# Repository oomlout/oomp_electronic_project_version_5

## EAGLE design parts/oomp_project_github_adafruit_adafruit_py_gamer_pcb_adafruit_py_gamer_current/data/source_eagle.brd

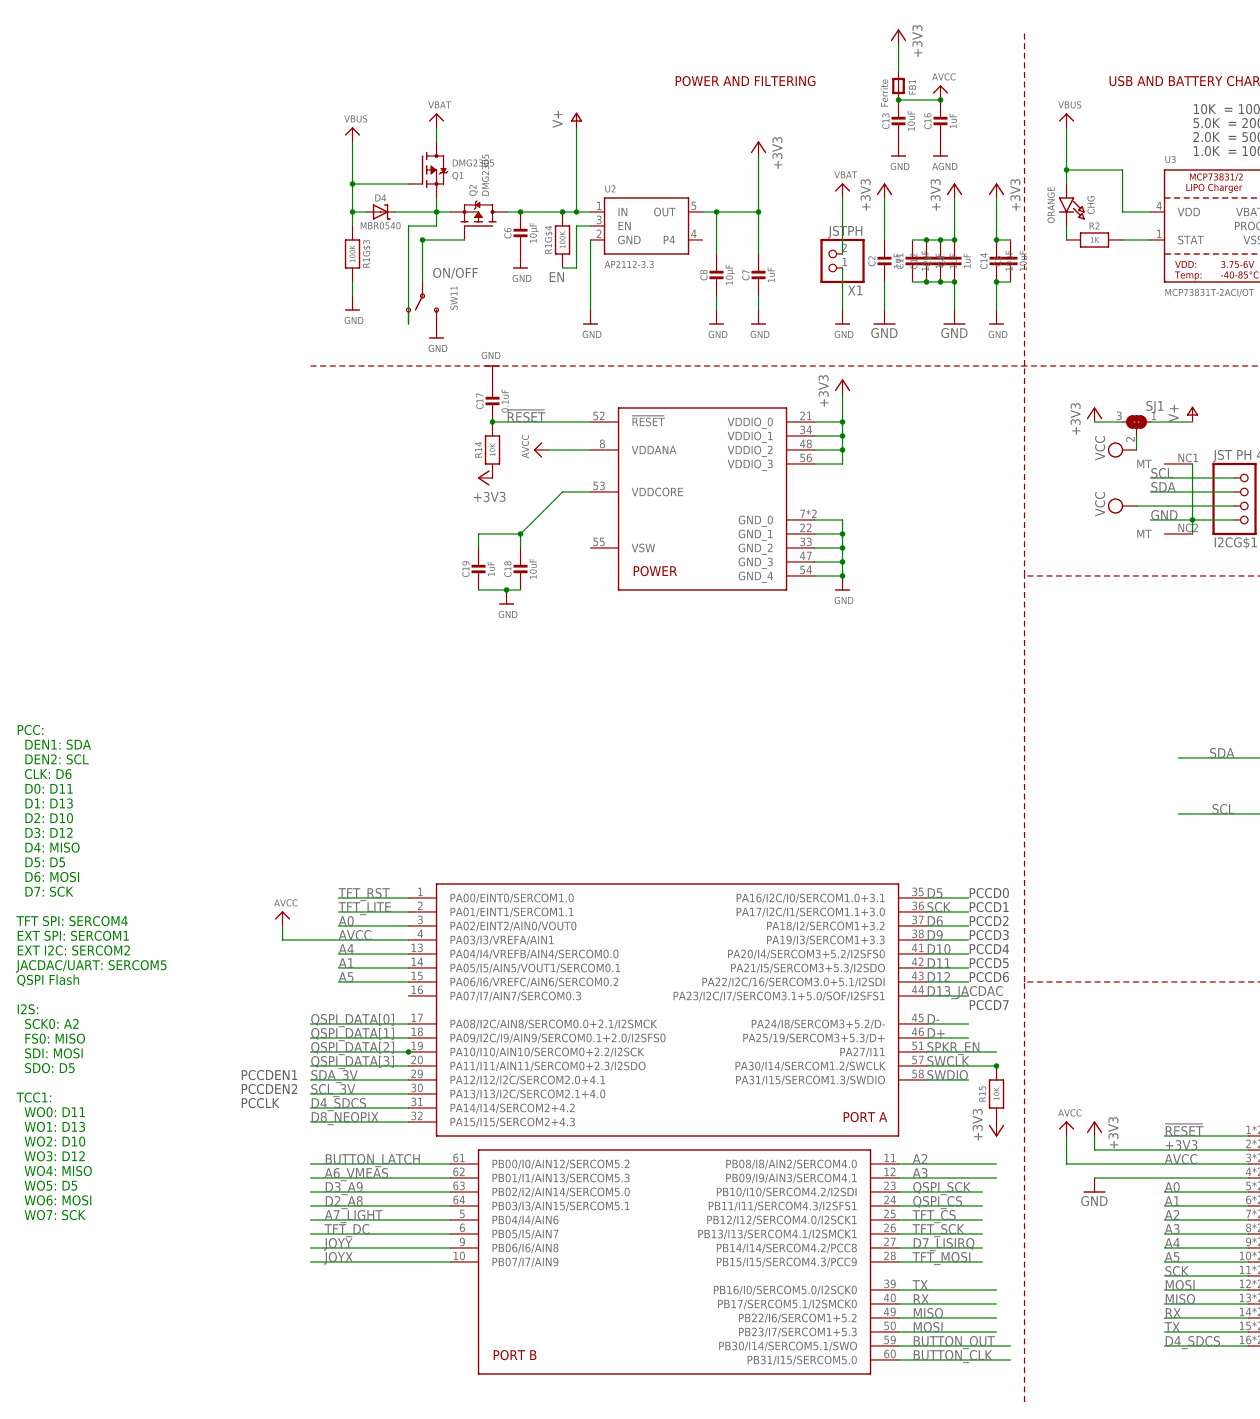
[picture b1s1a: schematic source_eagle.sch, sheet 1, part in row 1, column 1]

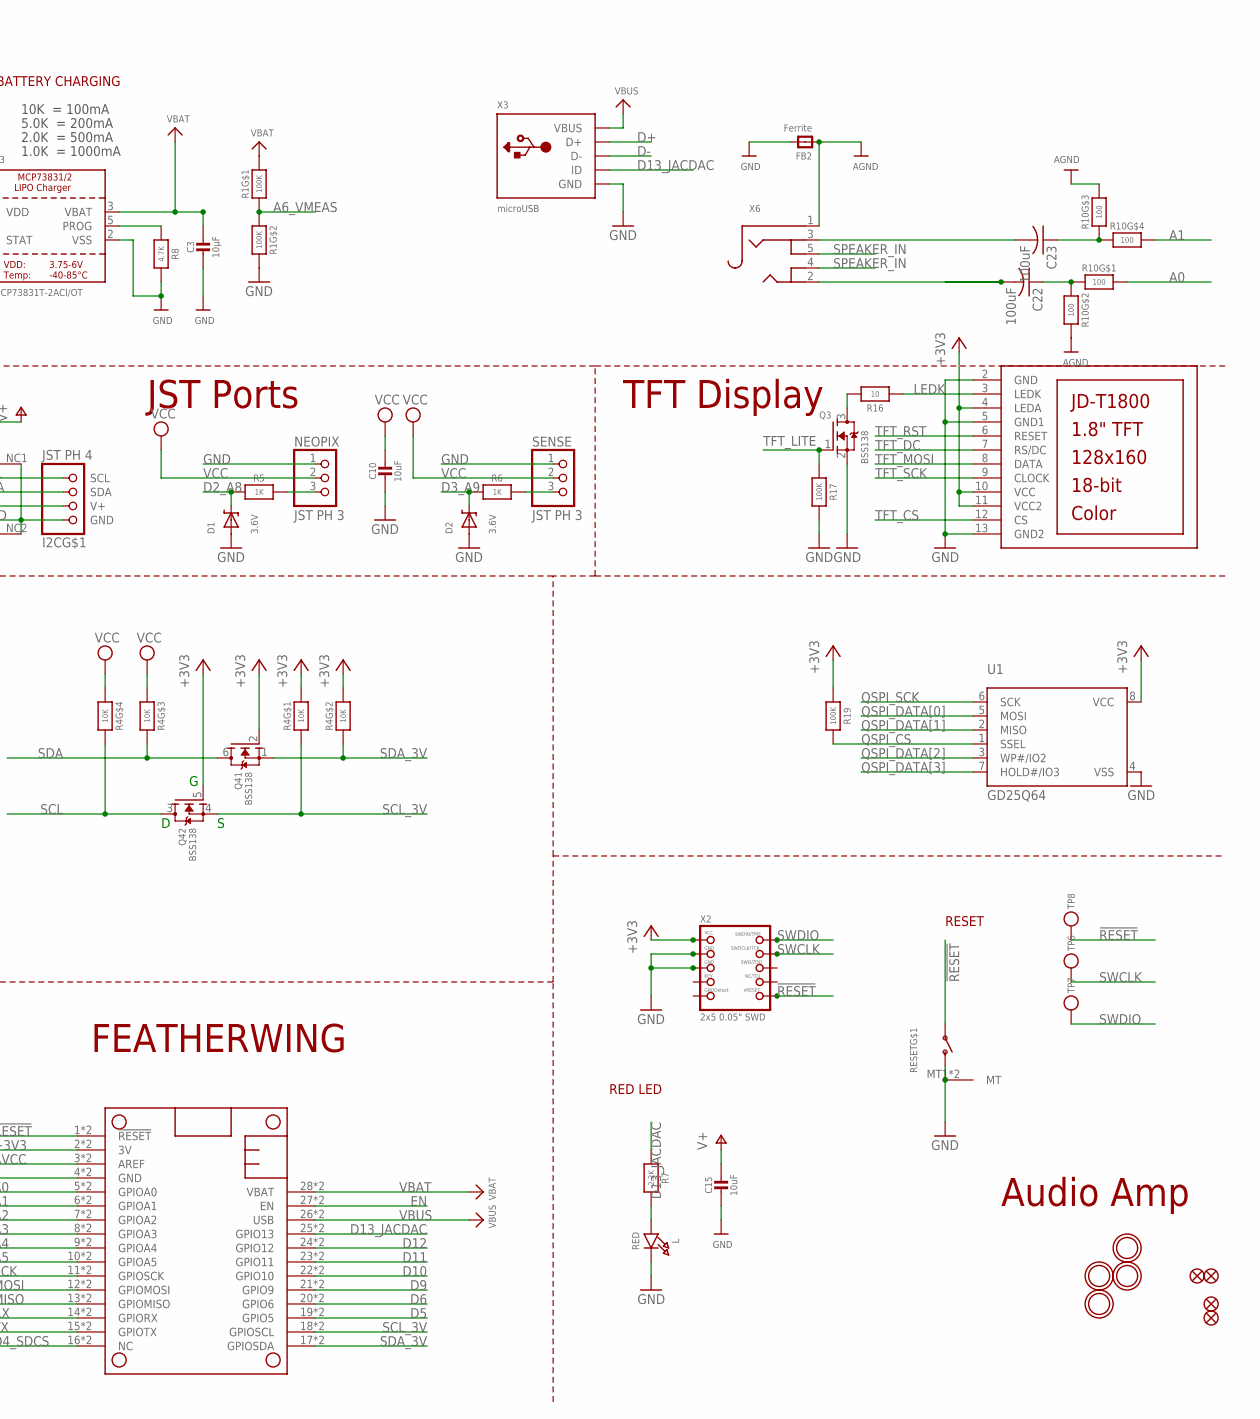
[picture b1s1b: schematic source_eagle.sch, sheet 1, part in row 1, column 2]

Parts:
C1, C2, C4, C7, C12, C16, C19: 1uF; 0603-NO
C3, C6, C8: 10µF; 0805-NO
C5, C10, C11, C13, C14, C15, C18: 10uF; 0805-NO
C17: 0.1uF; 0603-NO
C22, C23: 100uF; C1210
CHG: ORANGE; CHIPLED_0805_NOOUTLINE
D1, D2: 3.6V; SOD-323
D4: MBR0540; SOD-123
FB1: Ferrite; 0805-NO
FB2: Ferrite; _0805MP
I2C: JST PH 4; JSTPH4
L: RED; CHIPLED_0805_NOOUTLINE
LCD1: DISP_LCD_JDT1800; JD-T1800
MS1: FEATHERWING_SMTDUALNOHOLES; FEATHERWING_SMT_NOHOLES
NEOPIX: JST PH 3; JSTPH3
Q1, Q2: DMG2305; SOT23-R
Q3: BSS138; SOT23-WIDE
Q4: BSS138; SOT363
R1: 100K; RESPACK_4X0603
R2, R5, R6: 1K; 0603-NO
R4: 10K; RESPACK_4X0603
R7: 2.2K; 0603-NO
R8: 4.7K; 0603-NO
R10: 100; RESPACK_4X0603
R14, R15: 10K; 0603-NO
R16: 10; 0603-NO
R17, R19: 100K; 0603-NO
RESET: SWITCH_SPST_TACT_RA; SPST_TACTILE_RA
SENSE: JST PH 3; JSTPH3
SJ1: SOLDERJUMPER_2WAY; SOLDERJUMPER_2WAY_OPEN_NOPASTE
SW11: SWITCH_SPDT; SPDT_SMT_SSSS811101
TP6, TP7, TP8: TESTPOINTROUND2MMNO; TESTPOINT_ROUND_2MM_NO
U1: GD25Q64; SOIC8_208MIL
U2: AP2112-3.3; SOT23-5
U3: MCP73831T-2ACI/OT; SOT23-5
U$5, U$6, U$17, U$18: MOUNTINGHOLE3.0THIN; MOUNTINGHOLE_3.0_PLATEDTHIN
U$24: ATSAMD51J19; PQFN64-1
U$34, U$35, U$43, U$46: FIDUCIAL_1MM
X1: JSTPH; JSTPH2
X2: 2x5 0.05" SWD; 2X05_1.27MM_BOX_POSTS
X3: microUSB; 4UCONN_20329_V2
X6: AUDIO_3.5MMJACK; 4UCONN_19269

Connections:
!RESET: C17.2, MS1.1 (!RESET), MS1.1B (!RESET), R14.2, RESET.1, TP8.P$1, U$24.52 (!RESET), X2.10 (NRESET)
+3V3: C1.1, C2.1, C4.1, C5.1, C7.1, C8.1, C11.1, C12.1, C14.1, FB1.1, LCD1.4 (LEDA), LCD1.10 (VCC), LCD1.11 (VCC2), MS1.2 (3V), MS1.2B (3V), Q4.2 (G), Q4.5 (G), R4.1, R4.2 (1), R14.1, R15.1, R19.1, SJ1.3, U1.8 (VCC), U2.5 (OUT), U$24.21 (VDDIO_0), U$24.34 (VDDIO_1), U$24.48 (VDDIO_2), U$24.56 (VDDIO_3), X2.1 (VCC); also elsewhere on the board
A0: MS1.5 (GPIOA0), MS1.5B (GPIOA0), R10.8 (2), U$24.3 (PA02/EINT2/AIN0/VOUT0)
A1: MS1.6 (GPIOA1), MS1.6B (GPIOA1), R10.5 (2), U$24.14 (PA05/I5/AIN5/VOUT1/SERCOM0.1)
A2: MS1.7 (GPIOA2), MS1.7B (GPIOA2), U$24.11 (PB08/I8/AIN2/SERCOM4.0)
A3: MS1.8 (GPIOA3), MS1.8B (GPIOA3), U$24.12 (PB09/I9/AIN3/SERCOM4.1)
A4: MS1.9 (GPIOA4), MS1.9B (GPIOA4), U$24.13 (PA04/I4/VREFB/AIN4/SERCOM0.0)
A5: MS1.10 (GPIOA5), MS1.10B (GPIOA5), U$24.15 (PA06/I6/VREFC/AIN6/SERCOM0.2)
A6_VMEAS: R1.1, R1.2 (1), U$24.62 (PB01/I1/AIN13/SERCOM5.3)
A7_LIGHT: U$24.5 (PB04/I4/AIN6); also elsewhere on the board
AGND: C16.2, FB2.1, R10.6 (2), R10.7 (2), X6.1; also elsewhere on the board
AVCC: C13.1, C16.1, FB1.2, MS1.3 (AREF), MS1.3B (AREF), U$24.4 (PA03/I3/VREFA/AIN1), U$24.8 (VDDANA)
BUTTON_CLK: U$24.60 (PB31/I15/SERCOM5.0); also elsewhere on the board
BUTTON_LATCH: U$24.61 (PB00/I0/AIN12/SERCOM5.2); also elsewhere on the board
BUTTON_OUT: U$24.59 (PB30/I14/SERCOM5.1/SWO); also elsewhere on the board
CHG_LED: R2.2, U3.1 (STAT)
CHG_RATE: R8.1, U3.5 (PROG)
D2_: NEOPIX.3, R5.1
D2_A8: D1.C, R5.2, U$24.64 (PB03/I3/AIN15/SERCOM5.1)
D3_: R6.1, SENSE.3
D3_A9: D2.C, R6.2, U$24.63 (PB02/I2/AIN14/SERCOM5.0)
D4_SDCS: MS1.16 (NC), MS1.16B (NC), U$24.31 (PA14/I14/SERCOM2+4.2); also elsewhere on the board
D5: MS1.19 (GPIO5), MS1.19B (GPIO5), U$24.35 (PA16/I2C/I0/SERCOM1.0+3.1)
D6: MS1.20 (GPIO6), MS1.20B (GPIO6), U$24.37 (PA18/I2/SERCOM1+3.2)
D7_LISIRQ: U$24.27 (PB14/I14/SERCOM4.2/PCC8); also elsewhere on the board
D8_NEOPIX: U$24.32 (PA15/I15/SERCOM2+4.3); also elsewhere on the board
D9: MS1.21 (GPIO9), MS1.21B (GPIO9), U$24.38 (PA19/I3/SERCOM1+3.3)
D10: MS1.22 (GPIO10), MS1.22B (GPIO10), U$24.41 (PA20/I4/SERCOM3+5.2/I2SFS0)
D11: MS1.23 (GPIO11), MS1.23B (GPIO11), U$24.42 (PA21/I5/SERCOM3+5.3/I2SDO)
D12: MS1.24 (GPIO12), MS1.24B (GPIO12), U$24.43 (PA22/I2C/16/SERCOM3.0+5.1/I2SDI)
D13_JACDAC: MS1.25 (GPIO13), MS1.25B (GPIO13), R7.1, U$24.44 (PA23/I2C/I7/SERCOM3.1+5.0/SOF/I2SFS1), X3.ID
D+: U$24.46 (PA25/19/SERCOM3+5.3/D+), X3.D+
D-: U$24.45 (PA24/I8/SERCOM3+5.2/D-), X3.D-
EN: MS1.27 (EN), MS1.27B (EN), R1.4 (1), U2.3 (EN)
GND: C1.2, C2.2, C3.2, C4.2, C5.2, C6.2, C7.2, C8.2, C10.2, C11.2, C12.2, C13.2, C14.2, C15.2, C17.1, C18.2, C19.2, D1.A, D2.A, FB2.2, I2C.1 (GND), I2C.NC1 (MT), I2C.NC2 (MT), L.C, LCD1.2 (GND), LCD1.5 (GND1), LCD1.13 (GND2), MS1.4 (GND), MS1.4B (GND), NEOPIX.1, Q3.2 (S), R1.6 (2), R1.7 (2), R8.2, R17.2, RESET.2 (S), RESET.MT1 (MT), RESET.MT2 (MT), SENSE.1, SW11.C (S), U1.4 (VSS), U2.2 (GND), U3.2 (VSS), U$24.7 (GND_0), U$24.22 (GND_1), U$24.33 (GND_2), U$24.47 (GND_3), U$24.54 (GND_4), U$24.EXP (GND_0), X1.1, X2.3 (GND), X2.5 (GND), X3.BASE@1 (GND), X3.BASE@2 (GND), X3.GND, X3.SPRT@1 (GND), X3.SPRT@2 (GND), X3.SPRT@3 (GND), X3.SPRT@4 (GND); also elsewhere on the board
JOYX: U$24.10 (PB07/I7/AIN9); also elsewhere on the board
JOYY: U$24.9 (PB06/I6/AIN8); also elsewhere on the board
LEDK: LCD1.3 (LEDK), R16.1
MISO: MS1.13 (GPIOMISO), MS1.13B (GPIOMISO), U$24.49 (PB22/I6/SERCOM1+5.2); also elsewhere on the board
MOSI: MS1.12 (GPIOMOSI), MS1.12B (GPIOMOSI), U$24.50 (PB23/I7/SERCOM1+5.3); also elsewhere on the board
unnamed: CHG.C, R2.1
unnamed: L.A, R7.2
unnamed: Q3.3 (D), R16.2
unnamed: D4.C, Q1.2 (S), Q2.2 (S), SW11.A (O)
unnamed: C23.2, X6.3
unnamed: C22.2, X6.2
unnamed: C23.1, R10.3 (1), R10.4 (1)
unnamed: C22.1, R10.1, R10.2 (1)
ON/OFF: Q2.1 (G), SW11.B
QSPI_CS: R19.2, U1.1 (SSEL), U$24.24 (PB11/I11/SERCOM4.3/I2SFS1)
QSPI_DATA[0]: U1.5 (MOSI), U$24.17 (PA08/I2C/AIN8/SERCOM0.0+2.1/I2SMCK)
QSPI_DATA[1]: U1.2 (MISO), U$24.18 (PA09/I2C/I9/AIN9/SERCOM0.1+2.0/I2SFS0)
QSPI_DATA[2]: U1.3 (WP#/IO2), U$24.19 (PA10/I10/AIN10/SERCOM0+2.2/I2SCK)
QSPI_DATA[3]: U1.7 (HOLD#/IO3), U$24.20 (PA11/I11/AIN11/SERCOM0+2.3/I2SDO)
QSPI_SCK: U1.6 (SCK), U$24.23 (PB10/I10/SERCOM4.2/I2SDI)
RX: MS1.14 (GPIORX), MS1.14B (GPIORX), U$24.40 (PB17/SERCOM5.1/I2SMCK0)
SCK: MS1.11 (GPIOSCK), MS1.11B (GPIOSCK), U$24.36 (PA17/I2C/I1/SERCOM1.1+3.0); also elsewhere on the board
SCL: I2C.4 (SCL), Q4.3 (D), R4.5 (2)
SCL_3V: MS1.18 (GPIOSCL), MS1.18B (GPIOSCL), Q4.4 (S), R4.8 (2), U$24.30 (PA13/I13/I2C/SERCOM2.1+4.0); also elsewhere on the board
SDA: I2C.3 (SDA), Q4.6 (D), R4.6 (2)
SDA_3V: MS1.17 (GPIOSDA), MS1.17B (GPIOSDA), Q4.1 (S), R4.7 (2), U$24.29 (PA12/I12/I2C/SERCOM2.0+4.1); also elsewhere on the board
SPEAKER_IN: X6.4, X6.5; also elsewhere on the board
SPKR_EN: U$24.51 (PA27/I11); also elsewhere on the board
SWCLK: R15.2, TP6.P$1, U$24.57 (PA30/I14/SERCOM1.2/SWCLK), X2.4 (SWDCLK)
SWDIO: TP7.P$1, U$24.58 (PA31/I15/SERCOM1.3/SWDIO), X2.2 (SWDIO)
TFT_CS: LCD1.12 (CS), U$24.25 (PB12/I12/SERCOM4.0/I2SCK1)
TFT_DC: LCD1.7 (RS/DC), U$24.6 (PB05/I5/AIN7)
TFT_LITE: Q3.1 (G), R17.1, U$24.2 (PA01/EINT1/SERCOM1.1)
TFT_MOSI: LCD1.8 (DATA), U$24.28 (PB15/I15/SERCOM4.3/PCC9)
TFT_RST: LCD1.6 (RESET), U$24.1 (PA00/EINT0/SERCOM1.0)
TFT_SCK: LCD1.9 (CLOCK), U$24.26 (PB13/I13/SERCOM4.1/I2SMCK1)
TX: MS1.15 (GPIOTX), MS1.15B (GPIOTX), U$24.39 (PB16/I0/SERCOM5.0/I2SCK0)
V+: C6.1, C15.1, Q2.3 (D), R1.5 (2), SJ1.1, U2.1 (IN); also elsewhere on the board
VBAT: C3.1, MS1.28 (VBAT), MS1.28B (VBAT), Q1.3 (D), R1.8 (2), U3.3 (VBAT), X1.2
VBUS: CHG.A, D4.A, MS1.26 (USB), MS1.26B (USB), Q1.1 (G), R1.3 (1), U3.4 (VDD), X3.VBUS
VCC: C10.1, I2C.2 (V+), NEOPIX.2, R4.3 (1), R4.4 (1), SENSE.2, SJ1.2
VDDCORE2: C18.1, C19.1, U$24.53 (VDDCORE)

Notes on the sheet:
POWER AND FILTERING
RESET
10K = 100mA
5.0K = 200mA
2.0K = 500mA
1.0K = 1000mA
USB AND BATTERY CHARGING
RED LED
FEATHERWING
TFT Display
Audio Amp
JST Ports
PCCDEN1
PCCDEN2
PCCD0
PCCD1
PCCD2
PCCD3
PCCD4
PCCD5
PCCD6
PCCD7
PCCLK
PCC: DEN1: SDA DEN2: SCL CLK: D6 D0: D11 D1: D13 D2: D10 D3: D12 D4: MISO D5: D5 D6: MOSI D7: SCK TFT SPI: SERCOM4 EXT SPI: SERCOM1 EXT I2C: SERCOM2 JACDAC/UART: SERCOM5 QSPI Flash I2S: SCK0: A2 FS0: MISO SDI: MOSI SDO: D5 TCC1: WO0: D11 WO1: D13 WO2: D10 WO3: D12 WO4: MISO WO5: D5 WO6: MOSI WO7: S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

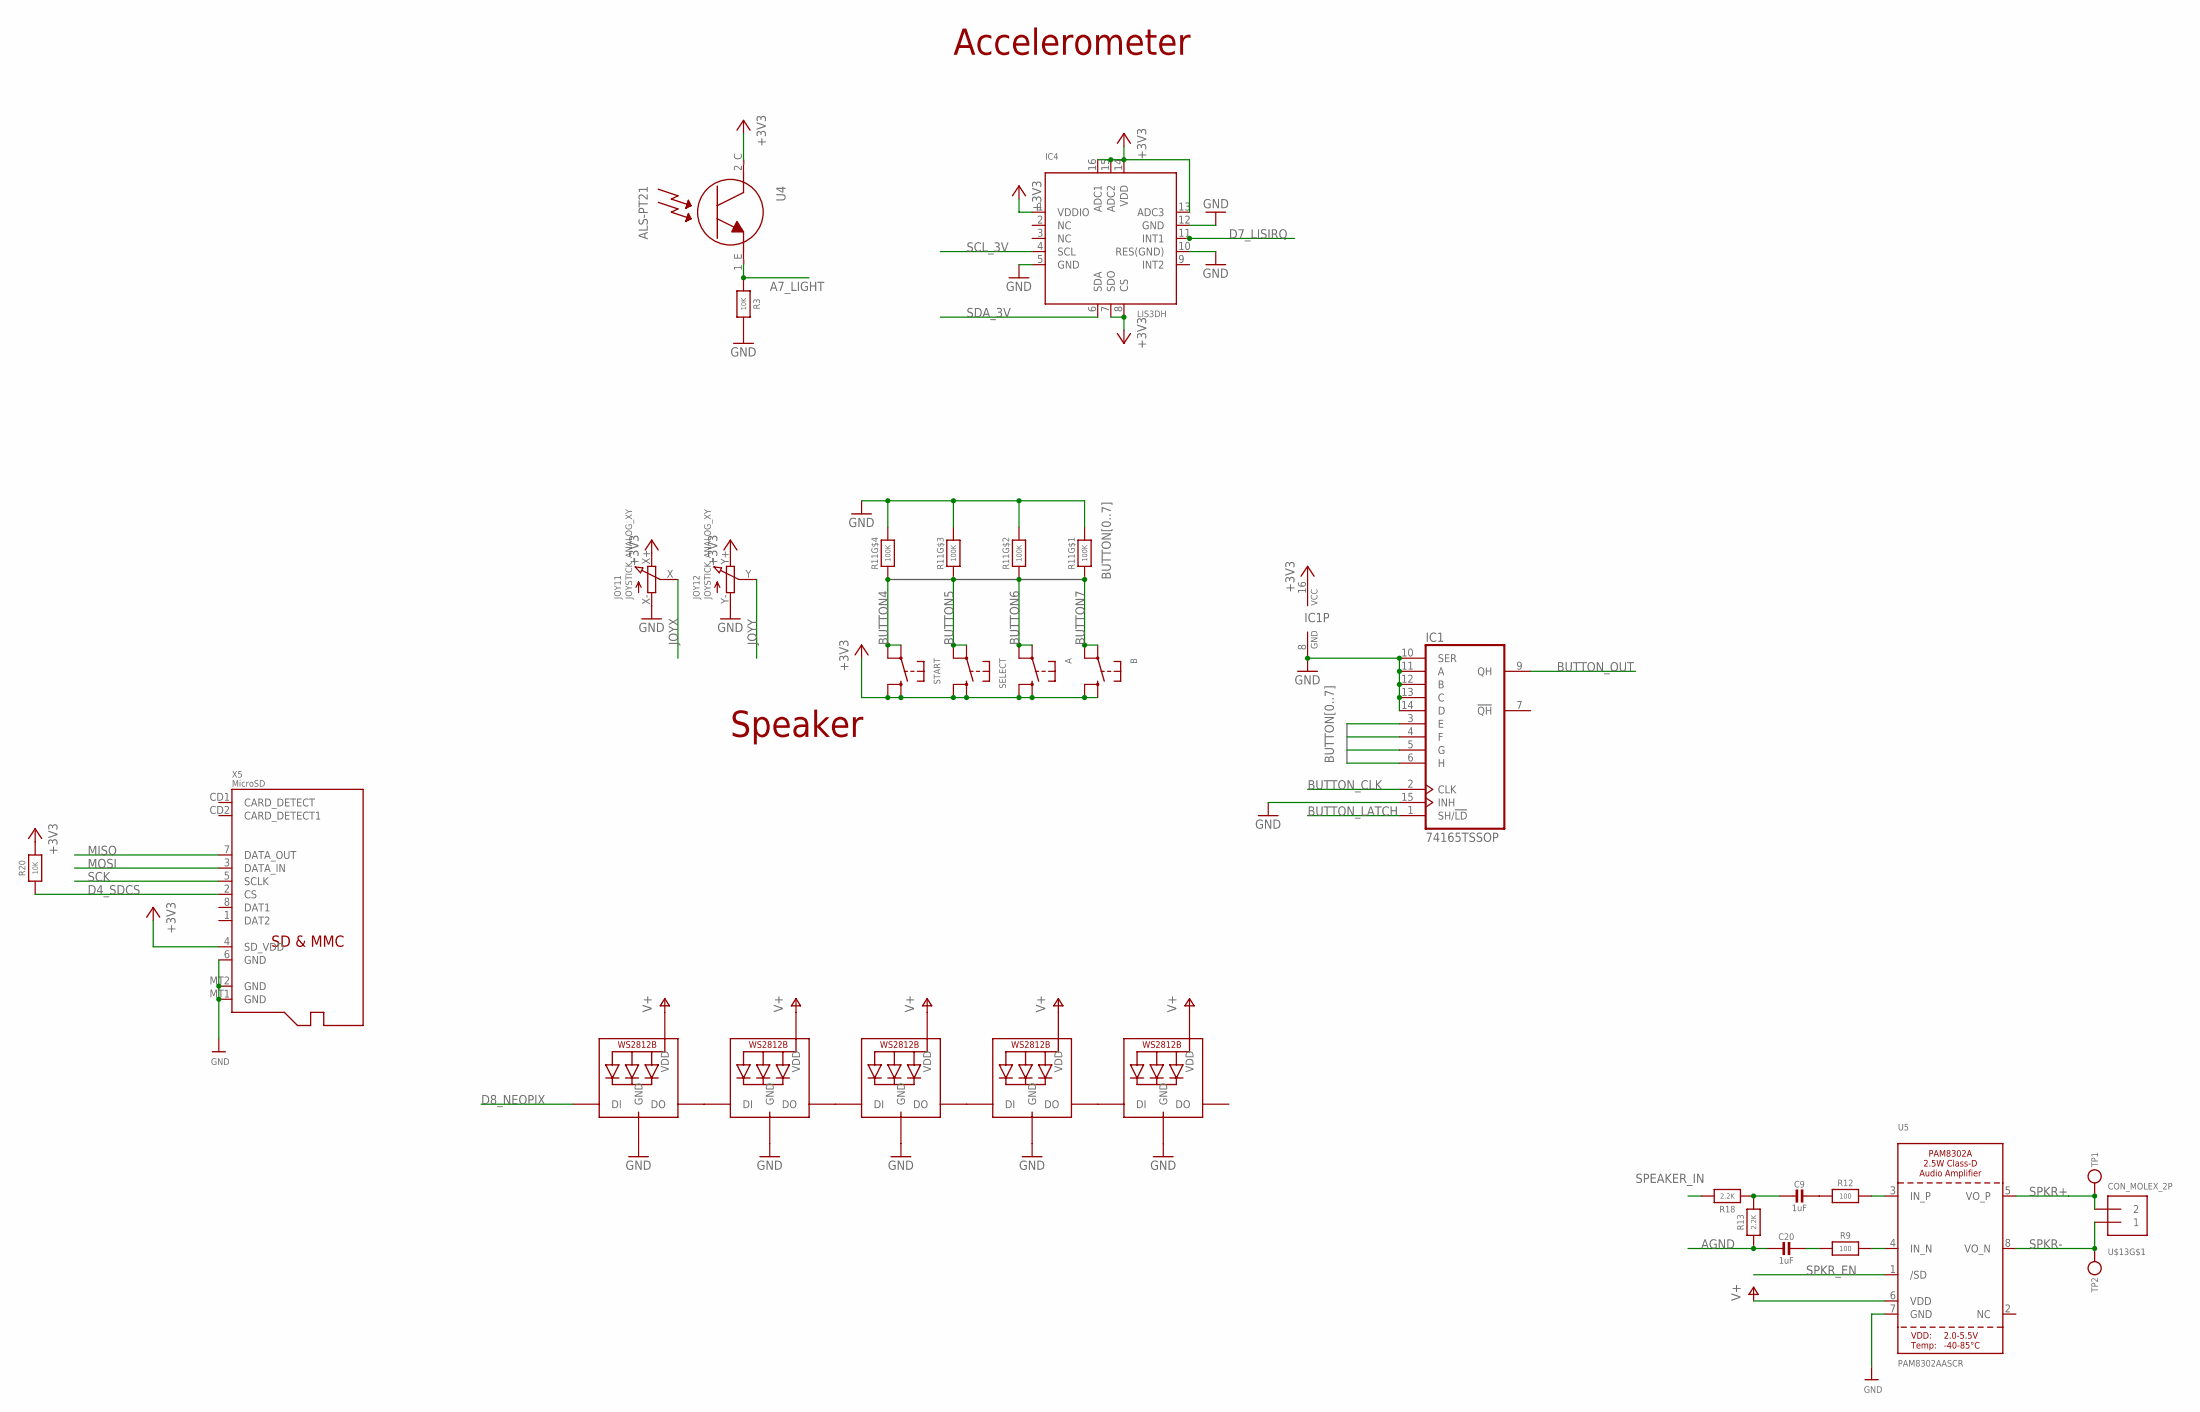
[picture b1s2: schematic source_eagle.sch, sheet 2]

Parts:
A: SWITCH_TACT_SMT_6MM8MMCAP; 6MM_SMT_6MMCAP
B: SWITCH_TACT_SMT_6MM8MMCAP; 6MM_SMT_6MMCAP
C9, C20: 1uF; 0603-NO
IC1: 74165TSSOP; TSSOP16
IC4: LIS3DH; LGA16_3X3MM
JOY1: JOYSTICK_ANALOG_XY; JOYSTICK_ANALOG_MINITHM
LED1, LED2, LED3, LED4, LED5: WS2812B3535; LED3535
R3, R20: 10K; 0603-NO
R9, R12: 100; 0603-NO
R11: 100K; RESPACK_4X0603
R13, R18: 2.2K; 0603-NO
SELECT: SWITCH_TACT_SMT_6MM8MMCAP; 6MM_SMT_6MMCAP
START: SWITCH_TACT_SMT_6MM8MMCAP; 6MM_SMT_6MMCAP
TP1, TP2: TESTPOINTROUND1.5MMNO; TESTPOINT_ROUND_1.5MM_NO
U4: ALS-PT21; ALS-PT26-21C
U5: PAM8302AASCR; MSOP8_0.65MM
U$13: CON_MOLEX_2P; 53398-0271
X5: MicroSD; MICROSD

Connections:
+3V3: A.B (S), A.B' (S1), B.B (S), B.B' (S1), IC1.16 (VCC), IC4.1 (VDDIO), IC4.7 (SDO), IC4.8 (CS), IC4.13 (ADC3), IC4.14 (VDD), IC4.15 (ADC2), IC4.16 (ADC1), JOY1.X+ (E), JOY1.Y+ (E), R20.2, SELECT.B (S), SELECT.B' (S1), START.B (S), START.B' (S1), U4.2_C (C), X5.4 (SD_VDD); also elsewhere on the board
A7_LIGHT: R3.2, U4.1_E (E); also elsewhere on the board
AGND: C20.2, R13.1; also elsewhere on the board
BUTTON4: IC1.3 (E), R11.4 (1), START.A, START.A' (P1)
BUTTON5: IC1.4 (F), R11.3 (1), SELECT.A, SELECT.A' (P1)
BUTTON6: A.A, A.A' (P1), IC1.5 (G), R11.2 (1)
BUTTON7: B.A, B.A' (P1), IC1.6 (H), R11.1
BUTTON_CLK: IC1.2 (CLK); also elsewhere on the board
BUTTON_LATCH: IC1.1 (SH/!LD); also elsewhere on the board
BUTTON_OUT: IC1.9 (QH); also elsewhere on the board
D4_SDCS: R20.1, X5.2 (CS); also elsewhere on the board
D7_LISIRQ: IC4.11 (INT1); also elsewhere on the board
D8_NEOPIX: LED1.1 (DI); also elsewhere on the board
GND: IC1.8 (GND), IC1.10 (SER), IC1.11 (A), IC1.12 (B), IC1.13 (C), IC1.14 (D), IC1.15 (INH), IC4.5 (GND), IC4.10 (RES(GND)), IC4.12 (GND), JOY1.X- (A), JOY1.Y- (A), LED1.4 (GND), LED2.4 (GND), LED3.4 (GND), LED4.4 (GND), LED5.4 (GND), R3.1, R11.5 (2), R11.6 (2), R11.7 (2), R11.8 (2), U5.7 (GND), X5.6 (GND), X5.MT1 (GND), X5.MT2 (GND); also elsewhere on the board
JOYX: JOY1.X (S); also elsewhere on the board
JOYY: JOY1.Y (S); also elsewhere on the board
MISO: X5.7 (DATA_OUT); also elsewhere on the board
MOSI: X5.3 (DATA_IN); also elsewhere on the board
unnamed: LED1.3 (DO), LED2.1 (DI)
unnamed: LED2.3 (DO), LED3.1 (DI)
unnamed: LED3.3 (DO), LED4.1 (DI)
unnamed: LED4.3 (DO), LED5.1 (DI)
unnamed: R9.2, U5.4 (IN_N)
unnamed: R12.2, U5.3 (IN_P)
unnamed: C9.2, R13.2, R18.1
unnamed: C20.1, R9.1
unnamed: C9.1, R12.1
SCK: X5.5 (SCLK); also elsewhere on the board
SCL_3V: IC4.4 (SCL); also elsewhere on the board
SDA_3V: IC4.6 (SDA); also elsewhere on the board
SPEAKER_IN: R18.2; also elsewhere on the board
SPKR+: TP1.P$1, U5.5 (VO_P), U$13.2
SPKR-: TP2.P$1, U5.8 (VO_N), U$13.1
SPKR_EN: U5.1 (/SD); also elsewhere on the board
V+: LED1.2 (VDD), LED2.2 (VDD), LED3.2 (VDD), LED4.2 (VDD), LED5.2 (VDD), U5.6 (VDD); also elsewhere on the board

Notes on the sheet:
Speaker
Accelerometer

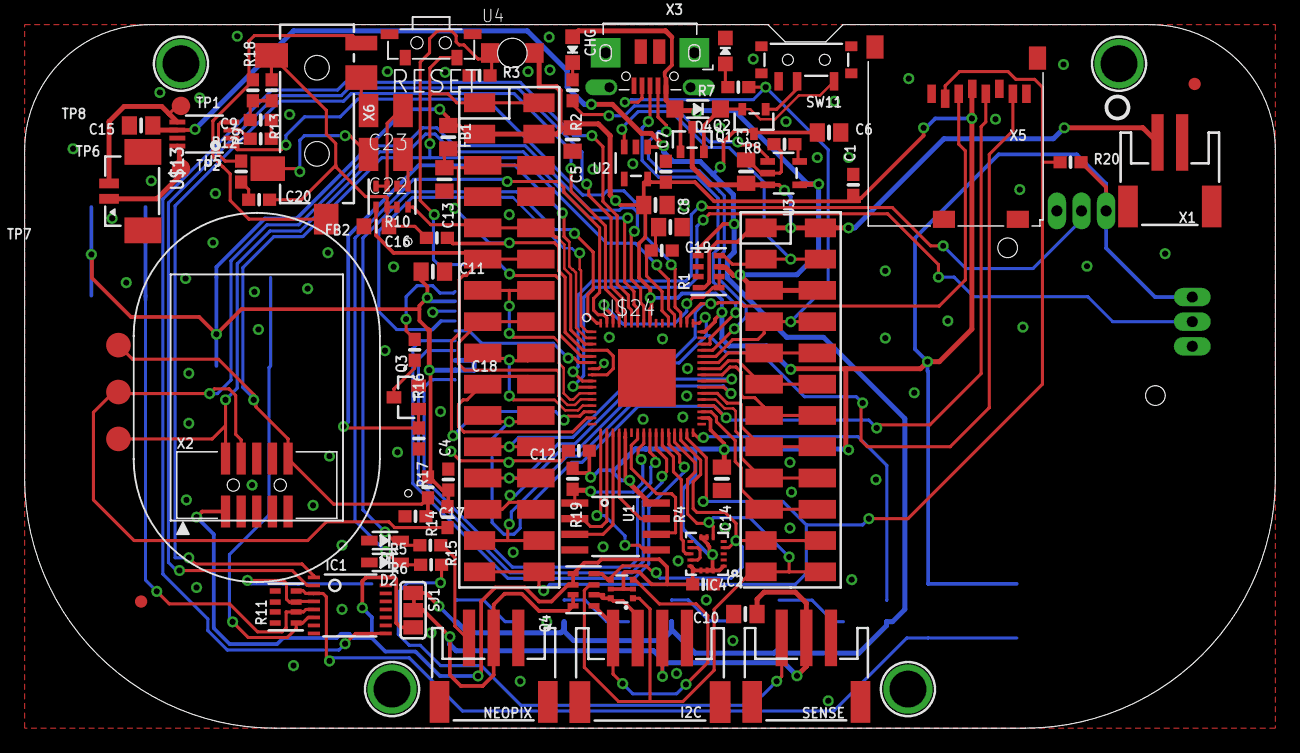
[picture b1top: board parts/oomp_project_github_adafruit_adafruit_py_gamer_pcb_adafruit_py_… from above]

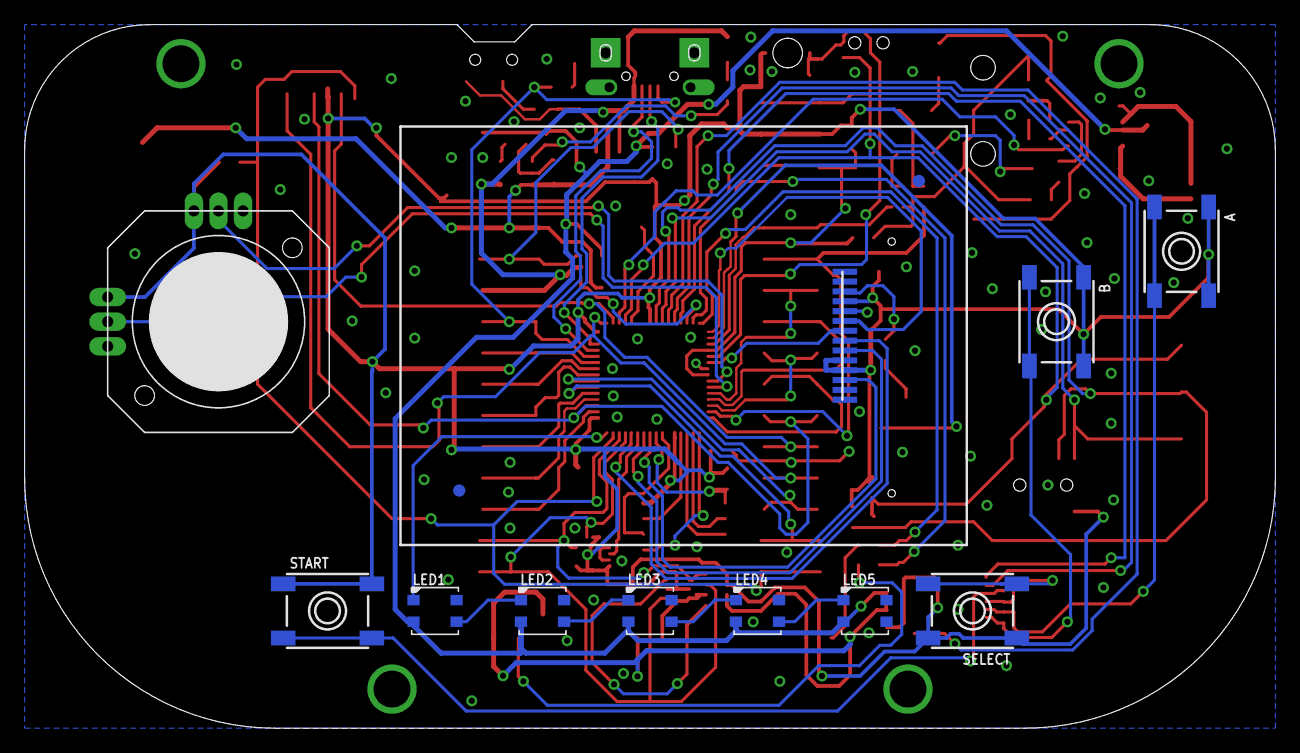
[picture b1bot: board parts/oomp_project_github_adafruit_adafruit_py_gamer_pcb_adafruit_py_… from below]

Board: 2 copper layers, 101.6 x 57.1 mm, 102 parts (14 on the bottom side), 92 nets.

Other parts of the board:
U$8: SPEAKER_OVAL8OHM
U$37: PCBFEAT-REV-040
U$47: PYGAMER_BACK
U$48: PYGAMER_FRONT

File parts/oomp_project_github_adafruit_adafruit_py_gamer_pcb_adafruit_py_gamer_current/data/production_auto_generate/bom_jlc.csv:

Comment,Designator,Footprint,LCSC Part #
,X6,Adafruit PyGamer-import-fps:4UCONN_19269,
,"A0,B0,SELECT0,START0",Adafruit PyGamer-import-fps:6MM_SMT_6MMCAP,
,U$37,Adafruit PyGamer-import-fps:PCBFEAT-REV-040,
,U$47,Adafruit PyGamer-import-fps:PYGAMER_BACK,
,U$48,Adafruit PyGamer-import-fps:PYGAMER_FRONT,
,SW11,Adafruit PyGamer-import-fps:SPDT_SMT_SSSS811101,
,U$8,Adafruit PyGamer-import-fps:SPEAKER_OVAL8OHM,
,RESET0,Adafruit PyGamer-import-fps:SPST_TACTILE_RA,
,"TP1,TP2",Adafruit PyGamer-import-fps:TESTPOINT_ROUND_1.5MM_NO,
,"TP6,TP7,TP8",Adafruit PyGamer-import-fps:TESTPOINT_ROUND_2MM_NO,
0.1uF,C17,Adafruit PyGamer-import-fps:0603-NO,C14663
10,R16,Adafruit PyGamer-import-fps:0603-NO,C22859
100,"R9,R12",Adafruit PyGamer-import-fps:0603-NO,C22775
100,R10,Adafruit PyGamer-import-fps:RESPACK_4X0603,C22775
100K,"R17,R19",Adafruit PyGamer-import-fps:0603-NO,C25803
100K,"R1,R11",Adafruit PyGamer-import-fps:RESPACK_4X0603,C25803
100uF,"C22,C23",Adafruit PyGamer-import-fps:C1210,
10K,"R3,R14,R15,R20",Adafruit PyGamer-import-fps:0603-NO,C98220
10K,R4,Adafruit PyGamer-import-fps:RESPACK_4X0603,C98220
10uF,"C5,C10,C11,C13,C14,C15,C18",Adafruit PyGamer-import-fps:0805-NO,
10µF,"C3,C6,C8",Adafruit PyGamer-import-fps:0805-NO,
1K,"R2,R5,R6",Adafruit PyGamer-import-fps:0603-NO,C2907002
1uF,"C1,C2,C4,C7,C9,C12,C16,C19,C20",Adafruit PyGamer-import-fps:0603-NO,C5673
2.2K,"R7,R13,R18",Adafruit PyGamer-import-fps:0603-NO,C4190
"2x5 0.05"" SWD",X2,Adafruit PyGamer-import-fps:2X05_1.27MM_BOX_POSTS,
3.6V,"D1,D2",Adafruit PyGamer-import-fps:SOD-323,
4.7K,R8,Adafruit PyGamer-import-fps:0603-NO,C23162
74165TSSOP,IC1,Adafruit PyGamer-import-fps:TSSOP16,
ALS-PT21,U4,Adafruit PyGamer-import-fps:ALS-PT26-21C,
AP2112-3.3,U2,Adafruit PyGamer-import-fps:SOT23-5,
ATSAMD51J19,U$24,Adafruit PyGamer-import-fps:PQFN64-1,
BSS138,Q3,Adafruit PyGamer-import-fps:SOT23-WIDE,C52895
BSS138,Q4,Adafruit PyGamer-import-fps:SOT363,
CON_MOLEX_2P,U$13,Adafruit PyGamer-import-fps:53398-0271,
DISP_LCD_JDT1800,LCD1,Adafruit PyGamer-import-fps:JD-T1800,
DMG2305,"Q1,Q2",Adafruit PyGamer-import-fps:SOT23-R,
FEATHERWING_SMTDUALNOHOLES,MS1,Adafruit PyGamer-import-fps:FEATHERWING_SMT_NOHOLES,
Ferrite,FB1,Adafruit PyGamer-import-fps:0805-NO,
Ferrite,FB2,Adafruit PyGamer-import-fps:_0805MP,
FIDUCIAL_1MM,"U$34,U$35,U$43,U$46",Adafruit PyGamer-import-fps:FIDUCIAL_1MM,
GD25Q64,U1,Adafruit PyGamer-import-fps:SOIC8_208MIL,
JOYSTICK_ANALOG_XY,JOY1,Adafruit PyGamer-import-fps:JOYSTICK_ANALOG_MINITHM,
JST PH 3,"NEOPIX0,SENSE0",Adafruit PyGamer-import-fps:JSTPH3,
JST PH 4,I2C0,Adafruit PyGamer-import-fps:JSTPH4,
JSTPH,X1,Adafruit PyGamer-import-fps:JSTPH2,
LIS3DH,IC4,Adafruit PyGamer-import-fps:LGA16_3X3MM,
MBR0540,D4,Adafruit PyGamer-import-fps:SOD-123,
MCP73831T-2ACI/OT,U3,Adafruit PyGamer-import-fps:SOT23-5,
MicroSD,X5,Adafruit PyGamer-import-fps:MICROSD,
microUSB,X3,Adafruit PyGamer-import-fps:4UCONN_20329_V2,
ORANGE,CHG0,Adafruit PyGamer-import-fps:CHIPLED_0805_NOOUTLINE,
PAM8302AASCR,U5,Adafruit PyGamer-import-fps:MSOP8_0.65MM,
RED,L0,Adafruit PyGamer-import-fps:CHIPLED_0805_NOOUTLINE,
WS2812B3535,"LED1,LED2,LED3,LED4,LED5",Adafruit PyGamer-import-fps:LED3535,

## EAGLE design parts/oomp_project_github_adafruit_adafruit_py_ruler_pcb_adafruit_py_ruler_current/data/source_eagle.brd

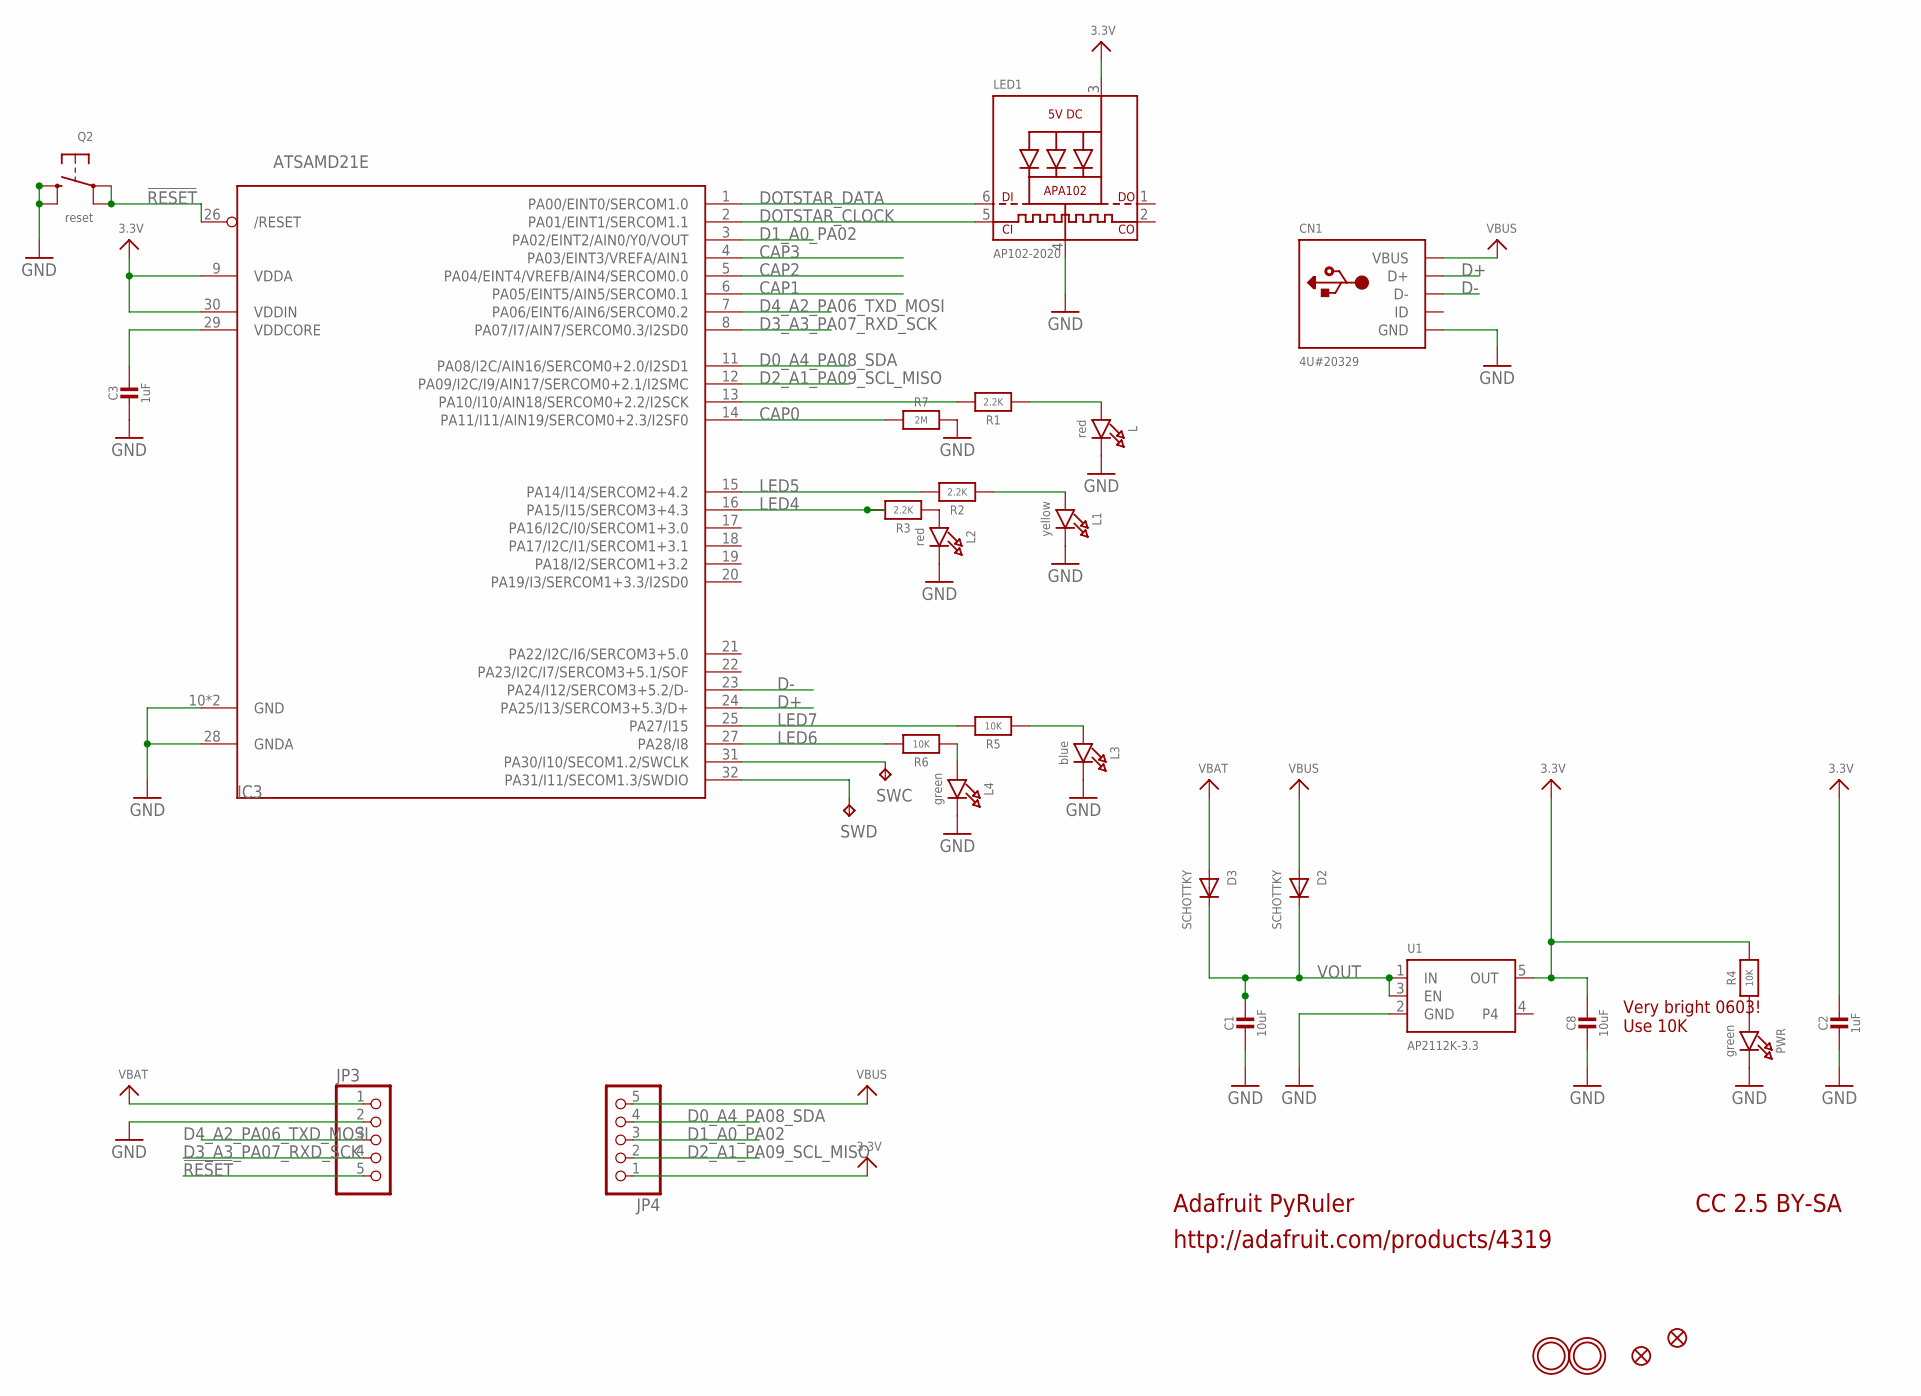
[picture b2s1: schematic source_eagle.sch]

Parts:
C1, C8: 10uF; 0805-NO
C2, C3: 1uF; 0603-NO
CN1: 4U#20329; 4UCONN_20329_NARROW
D2, D3: SCHOTTKY; SOD-123FL
IC3: ATSAMD21E; QFN32_5MM
JP3, JP4: HEADER-1X570MIL; 1X05_ROUND_70
L, L2: red; CHIPLED_0603_NOOUTLINE
L1: yellow; CHIPLED_0603_NOOUTLINE
L3: blue; CHIPLED_0603_NOOUTLINE
L4: green; CHIPLED_0603_NOOUTLINE
LED1: AP102-2020; APA102_2020
PWR: green; CHIPLED_0603_NOOUTLINE
Q2: reset; BTN_KMR2_4.6X2.8
R1, R2, R3: 2.2K; 0603-NO
R4, R5, R6: 10K; 0603-NO
R7: 2M; 0603-NO
SWC: TPB1,27; B1,27
SWD: TPB1,27; B1,27
U1: AP2112K-3.3; SOT23-5
U$1, U$6: FIDUCIAL_1MM
U$8, U$9: MOUNTINGHOLE2.0; MOUNTINGHOLE_2.0_PLATED

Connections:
3.3V: C2.1, C8.1, IC3.9 (VDDA), IC3.30 (VDDIN), JP4.1, LED1.3 (VDD), R4.2, U1.5 (OUT)
!RESET: IC3.26 (/RESET), JP3.5, Q2.A, Q2.A' (P1)
CAP0: IC3.14 (PA11/I11/AIN19/SERCOM0+2.3/I2SF0), R7.1
CAP1: IC3.6 (PA05/EINT5/AIN5/SERCOM0.1)
CAP2: IC3.5 (PA04/EINT4/VREFB/AIN4/SERCOM0.0)
CAP3: IC3.4 (PA03/EINT3/VREFA/AIN1)
D0_A4_PA08_SDA: IC3.11 (PA08/I2C/AIN16/SERCOM0+2.0/I2SD1), JP4.4
D1_A0_PA02: IC3.3 (PA02/EINT2/AIN0/Y0/VOUT), JP4.3
D2_A1_PA09_SCL_MISO: IC3.12 (PA09/I2C/I9/AIN17/SERCOM0+2.1/I2SMC), JP4.2
D3_A3_PA07_RXD_SCK: IC3.8 (PA07/I7/AIN7/SERCOM0.3/I2SD0), JP3.4
D4_A2_PA06_TXD_MOSI: IC3.7 (PA06/EINT6/AIN6/SERCOM0.2), JP3.3
D+: CN1.D+, IC3.24 (PA25/I13/SERCOM3+5.3/D+)
D-: CN1.D-, IC3.23 (PA24/I12/SERCOM3+5.2/D-)
DOTSTAR_CLOCK: IC3.2 (PA01/EINT1/SERCOM1.1), LED1.5 (CKI)
DOTSTAR_DATA: IC3.1 (PA00/EINT0/SERCOM1.0), LED1.6 (DI)
GND: C1.2, C2.2, C3.2, C8.2, CN1.BASE@1 (GND), CN1.BASE@2 (GND), CN1.GND, CN1.SPRT@1 (GND), CN1.SPRT@2 (GND), CN1.SPRT@3 (GND), CN1.SPRT@4 (GND), IC3.10 (GND), IC3.28 (GNDA), IC3.33 (GND), JP3.2, L.C, L1.C, L2.C, L3.C, L4.C, LED1.4 (GND), PWR.C, Q2.B (S), Q2.B' (S1), R7.2, U1.2 (GND)
LED: IC3.13 (PA10/I10/AIN18/SERCOM0+2.2/I2SCK), R1.2
LED4: IC3.16 (PA15/I15/SERCOM3+4.3), R3.2
LED5: IC3.15 (PA14/I14/SERCOM2+4.2), R2.2
LED6: IC3.27 (PA28/I8), R6.2
LED7: IC3.25 (PA27/I15), R5.2
unnamed: L.A, R1.1
unnamed: IC3.31 (PA30/I10/SECOM1.2/SWCLK), SWC.TP
unnamed: IC3.32 (PA31/I11/SECOM1.3/SWDIO), SWD.TP
unnamed: PWR.A, R4.1
unnamed: L1.A, R2.1
unnamed: L2.A, R3.1
unnamed: L4.A, R6.1
unnamed: L3.A, R5.1
VBAT: D3.A, JP3.1
VBUS: CN1.VBUS, D2.A, JP4.5
VDDCORE: C3.1, IC3.29 (VDDCORE)
VOUT: C1.1, D2.C, D3.C, U1.1 (IN), U1.3 (EN)

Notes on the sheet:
Adafruit PyRuler
http://adafruit.com/products/4319
CC 2.5 BY-SA
Very bright 0603! Use 10K

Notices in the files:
parts and their libraries:
microbuilder: This work is placed in the public domain, and may be freely used for commercial and non-commercial work with the following conditions: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
